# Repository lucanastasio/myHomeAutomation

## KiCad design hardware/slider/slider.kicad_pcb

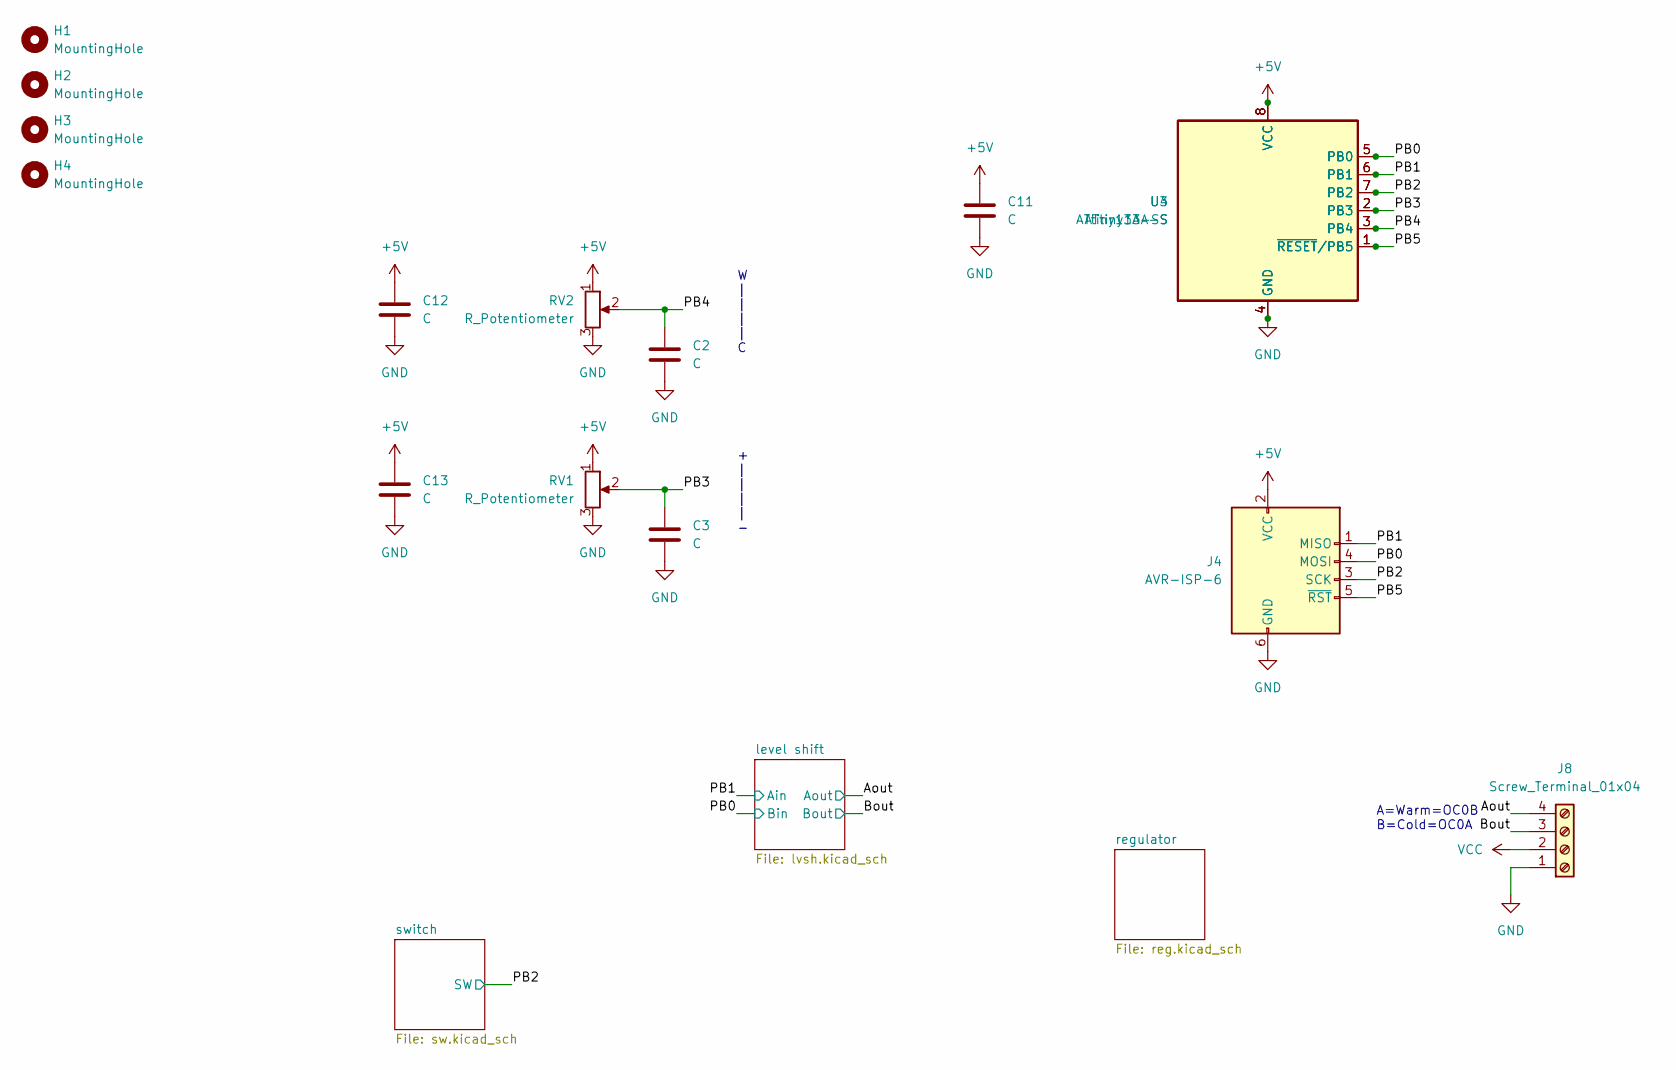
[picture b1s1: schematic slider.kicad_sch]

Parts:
C2, C3, C11, C12, C13: C; C_0603_1608Metric_Pad1.08x0.95mm_HandSolder
H1, H2, H3, H4: MountingHole; MountingHole_2.1mm
J4: AVR-ISP-6; PinHeader_2x03_P2.54mm_Vertical
J8: Screw_Terminal_01x04; PhoenixContact_MCV_1,5_4-G-3.81_1x04_P3.81mm_Vertical
RV1, RV2: R_Potentiometer; Alpha_RA2043F-20
U3: ATtiny13A-S; SOIC-8W_5.3x5.3mm_P1.27mm
U4: ATtiny13A-SS; SOIC-8_3.9x4.9mm_P1.27mm

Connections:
+5V: C11.1, C12.1, C13.1, J4.2 (VCC), RV1.1, RV2.1, U3.8 (VCC), U4.8 (VCC); also elsewhere on the board
/Aout: J8.4; also elsewhere on the board
/Bout: J8.3; also elsewhere on the board
/PB0: J4.4 (MOSI), U3.5 (PB0), U4.5 (PB0); also elsewhere on the board
/PB1: J4.1 (MISO), U3.6 (PB1), U4.6 (PB1); also elsewhere on the board
/PB2: J4.3 (SCK), U3.7 (PB2), U4.7 (PB2); also elsewhere on the board
/PB3: C3.1, RV1.2, U3.2 (PB3), U4.2 (PB3)
/PB4: C2.1, RV2.2, U3.3 (PB4), U4.3 (PB4)
/PB5: J4.5 (~RST), U3.1 (~RESET/PB5), U4.1 (~RESET/PB5)
GND: C2.2, C3.2, C11.2, C12.2, C13.2, J4.6 (GND), J8.1, RV1.3, RV2.3, U3.4 (GND), U4.4 (GND); also elsewhere on the board
VCC: J8.2; also elsewhere on the board

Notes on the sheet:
+ | | | | -
A=Warm=OC0B B=Cold=OC0A
W | | | | C

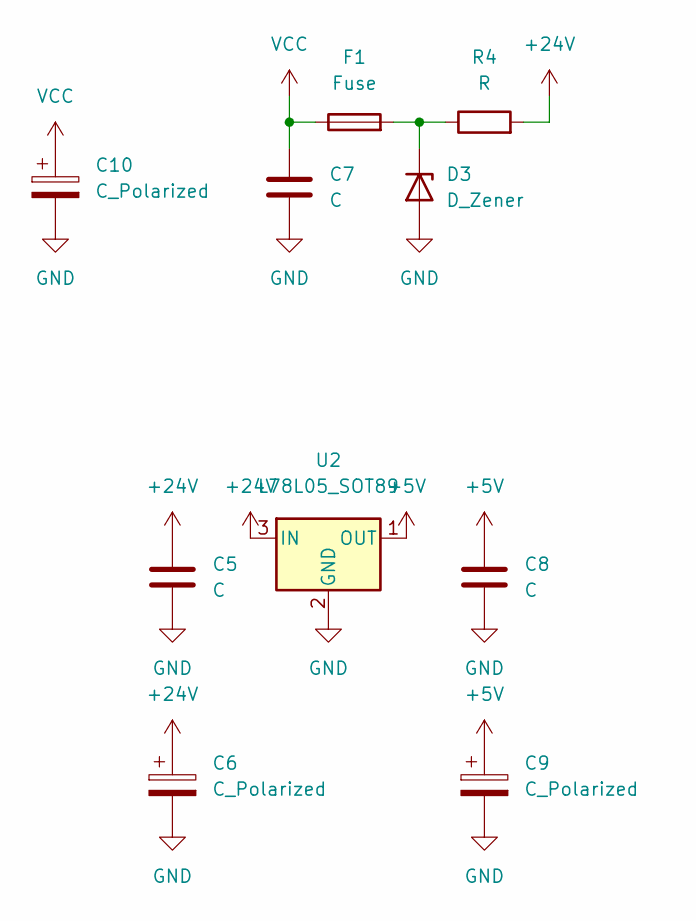
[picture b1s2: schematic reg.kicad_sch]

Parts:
C5, C7, C8: C; C_0603_1608Metric_Pad1.08x0.95mm_HandSolder
C6, C9: C_Polarized; CP_Elec_6.3x5.4
C10: C_Polarized; CP_Elec_8x6.7
D3: D_Zener; Nexperia_CFP3_SOD-123W
F1: Fuse; Fuse_1206_3216Metric_Pad1.42x1.75mm_HandSolder
R4: R; R_0805_2012Metric_Pad1.20x1.40mm_HandSolder
U2: L78L05_SOT89; SOT-89-3

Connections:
+5V: C8.1, C9.1, U2.1 (OUT); also elsewhere on the board
+24V: C5.1, C6.1, R4.2, U2.3 (IN); also elsewhere on the board
GND: C5.2, C6.2, C7.2, C8.2, C9.2, C10.2, D3.2 (A), U2.2 (GND); also elsewhere on the board
unnamed: D3.1 (K), F1.2, R4.1
VCC: C7.1, C10.1, F1.1; also elsewhere on the board

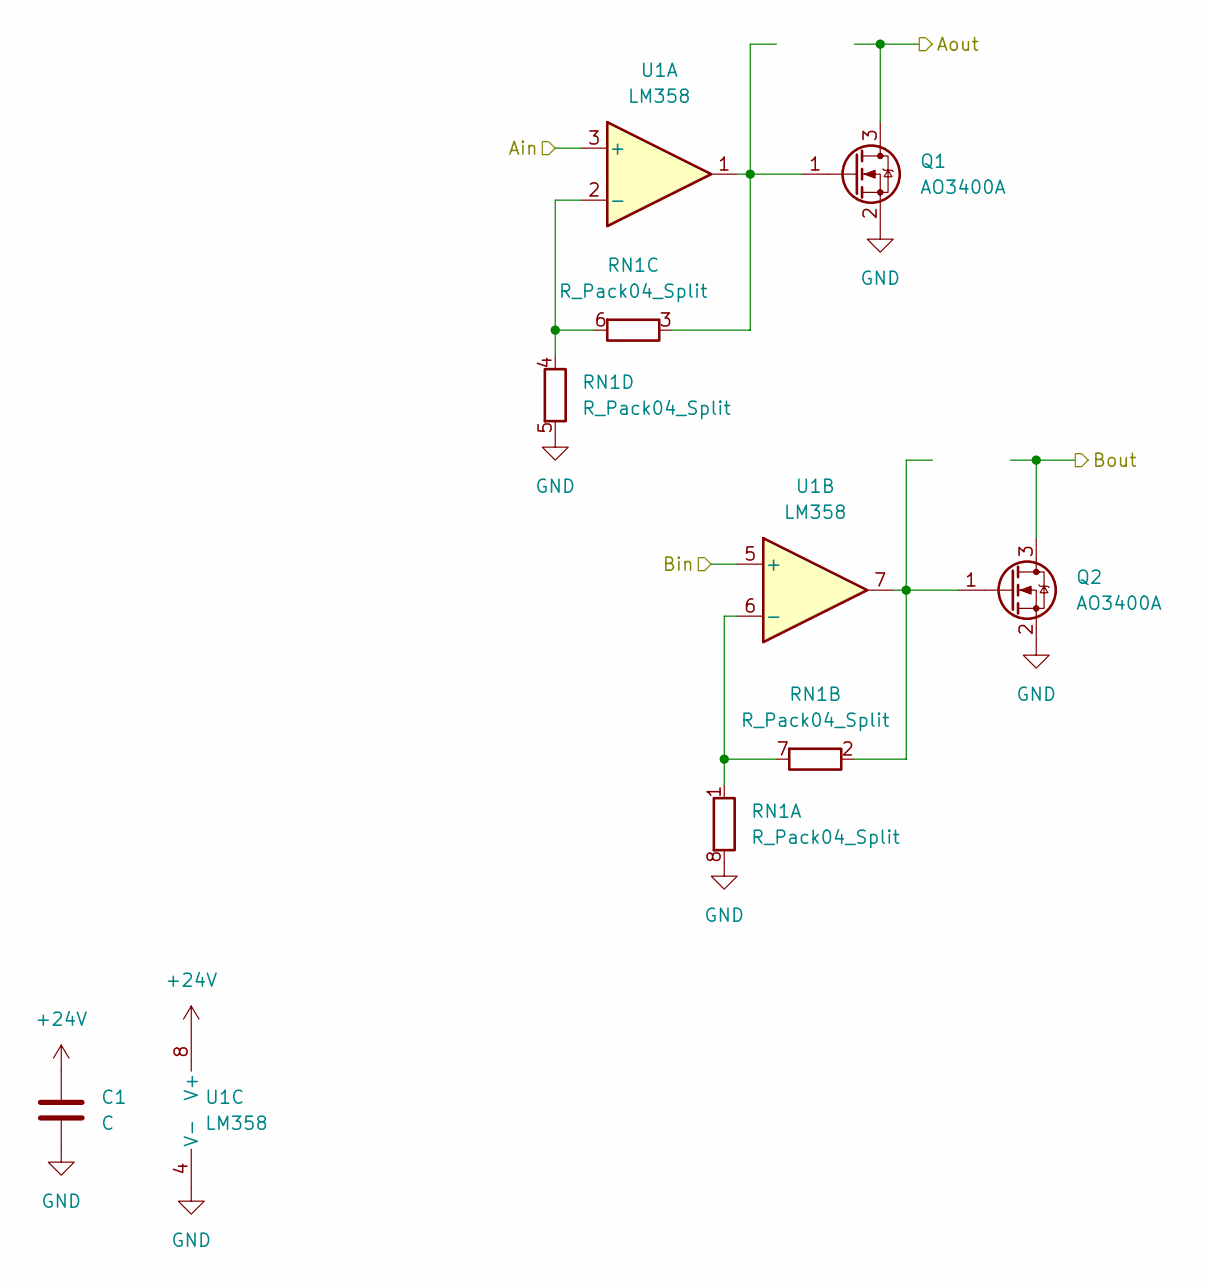
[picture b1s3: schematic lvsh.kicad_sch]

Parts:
C1: C; C_0603_1608Metric_Pad1.08x0.95mm_HandSolder
Q1, Q2: AO3400A; SOT-23W_Handsoldering
RN1: R_Pack04_Split; R_Array_Convex_4x0603
U1: LM358; SOIC-8_3.9x4.9mm_P1.27mm

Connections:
+24V: C1.1, U1.8 (V+); also elsewhere on the board
/Aout: Q1.3 (D); also elsewhere on the board
/Bout: Q2.3 (D); also elsewhere on the board
/PB0: U1.5 (+); also elsewhere on the board
/PB1: U1.3 (+); also elsewhere on the board
GND: C1.2, Q1.2 (S), Q2.2 (S), RN1.5 (R4.2), RN1.8 (R1.2), U1.4 (V-); also elsewhere on the board
unnamed: Q1.1 (G), RN1.3 (R3.1), U1.1
unnamed: Q2.1 (G), RN1.2 (R2.1), U1.7
unnamed: RN1.1 (R1.1), RN1.7 (R2.2), U1.6 (-)
unnamed: RN1.4 (R4.1), RN1.6 (R3.2), U1.2 (-)

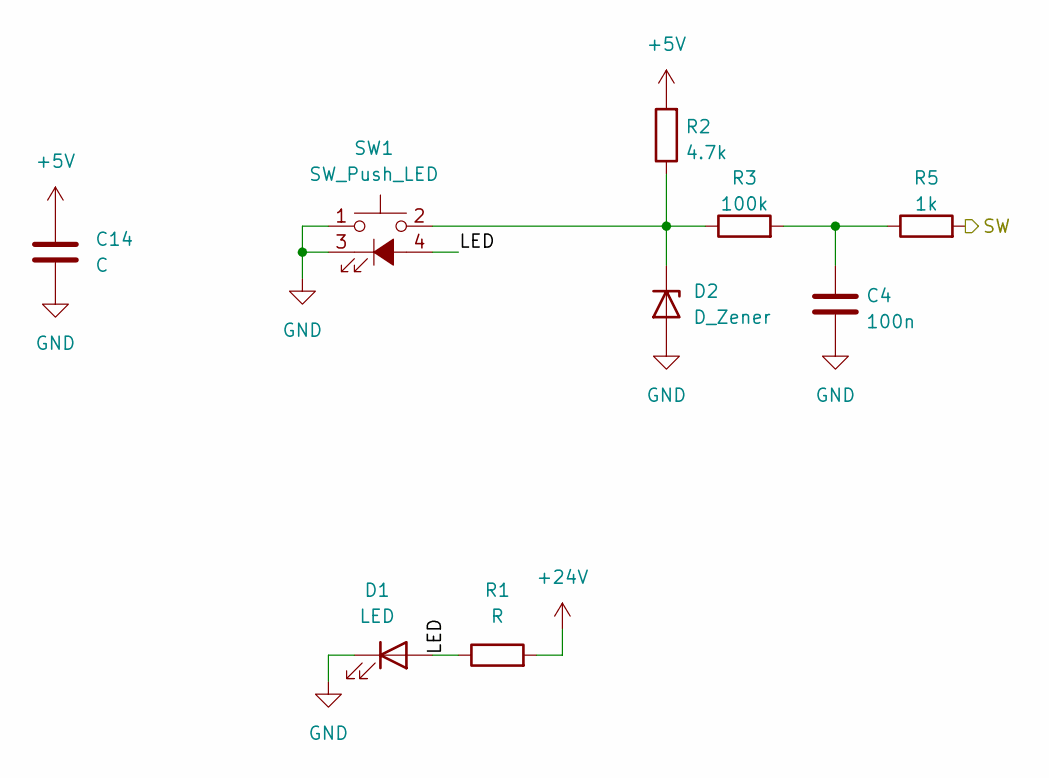
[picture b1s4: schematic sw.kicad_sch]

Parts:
C4: 100n; C_0603_1608Metric_Pad1.08x0.95mm_HandSolder
C14: C; C_0603_1608Metric_Pad1.08x0.95mm_HandSolder
D1: LED; LED_D5.0mm_Clear
D2: D_Zener; Nexperia_CFP3_SOD-123W
R1: R; R_0603_1608Metric_Pad0.98x0.95mm_HandSolder
R2: 4.7k; R_0603_1608Metric_Pad0.98x0.95mm_HandSolder
R3: 100k; R_0603_1608Metric_Pad0.98x0.95mm_HandSolder
R5: 1k; R_0603_1608Metric_Pad0.98x0.95mm_HandSolder
SW1: SW_Push_LED; SW_PUSH-12mm_LED

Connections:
+5V: C14.1, R2.2; also elsewhere on the board
+24V: R1.2; also elsewhere on the board
/PB2: R5.2; also elsewhere on the board
/switch/LED: D1.2 (A), R1.1, SW1.4 (A)
GND: C4.2, C14.2, D1.1 (K), D2.2 (A), SW1.1, SW1.3 (K); also elsewhere on the board
unnamed: C4.1, R3.2, R5.1
unnamed: D2.1 (K), R2.1, R3.1, SW1.2

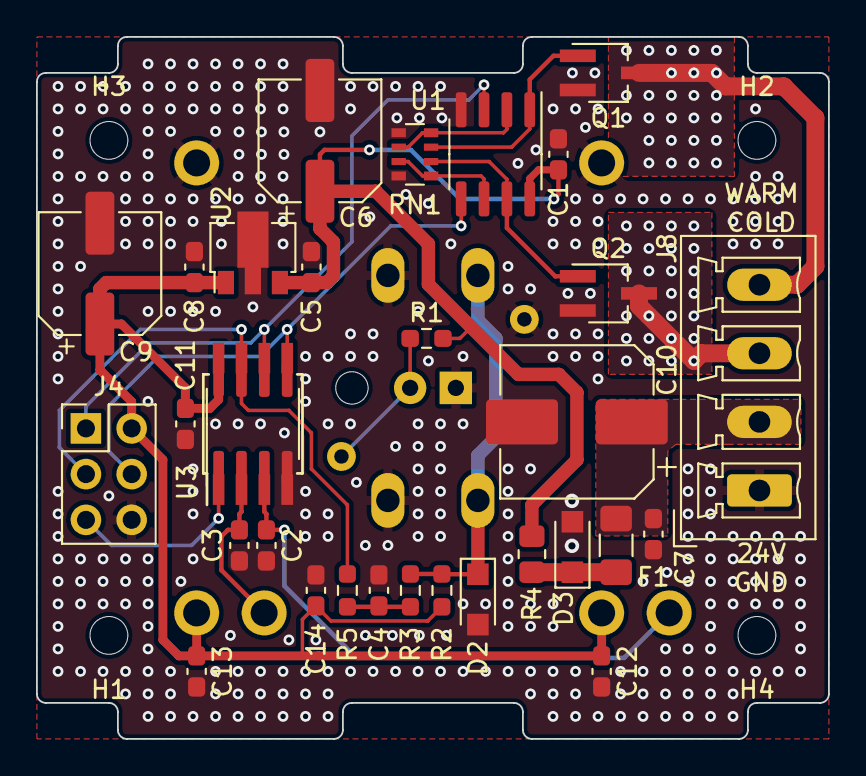
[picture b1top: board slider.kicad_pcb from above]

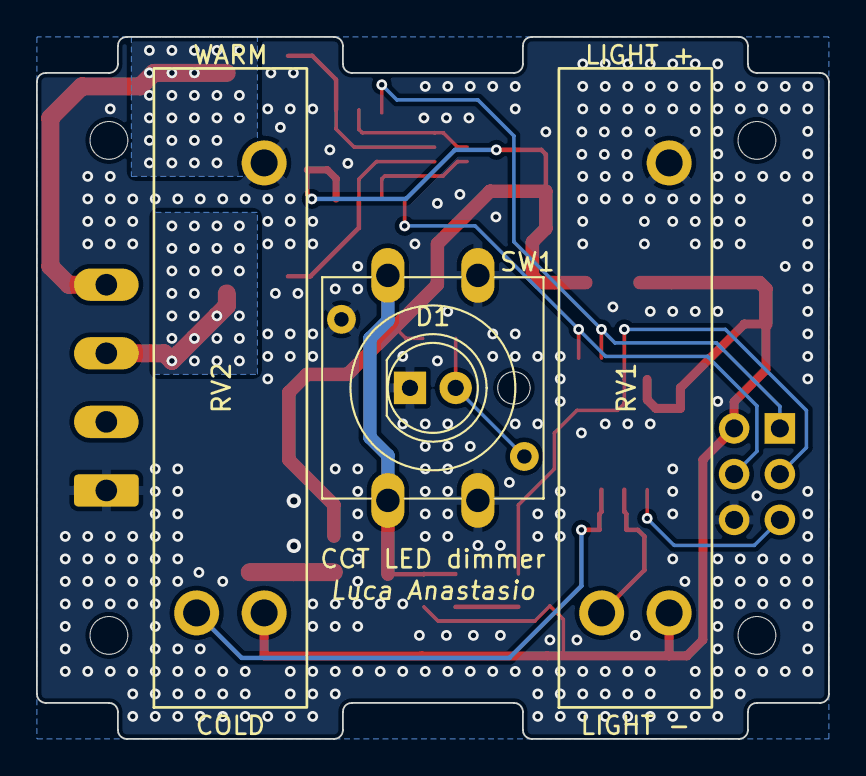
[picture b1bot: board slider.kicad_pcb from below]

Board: 2 copper layers, 44.0 x 39.0 mm, 39 parts (4 on the bottom side), 20 nets.

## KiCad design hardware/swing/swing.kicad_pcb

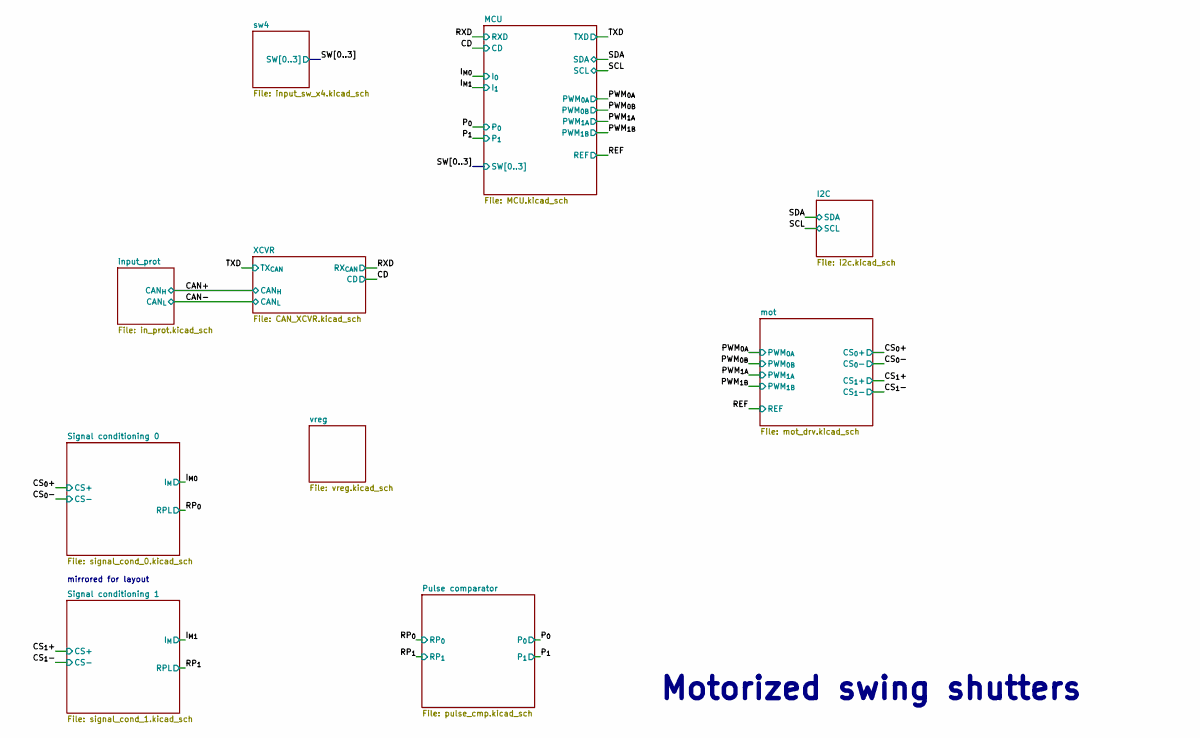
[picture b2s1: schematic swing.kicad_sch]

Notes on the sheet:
Motorized swing shutters
mirrored for layout

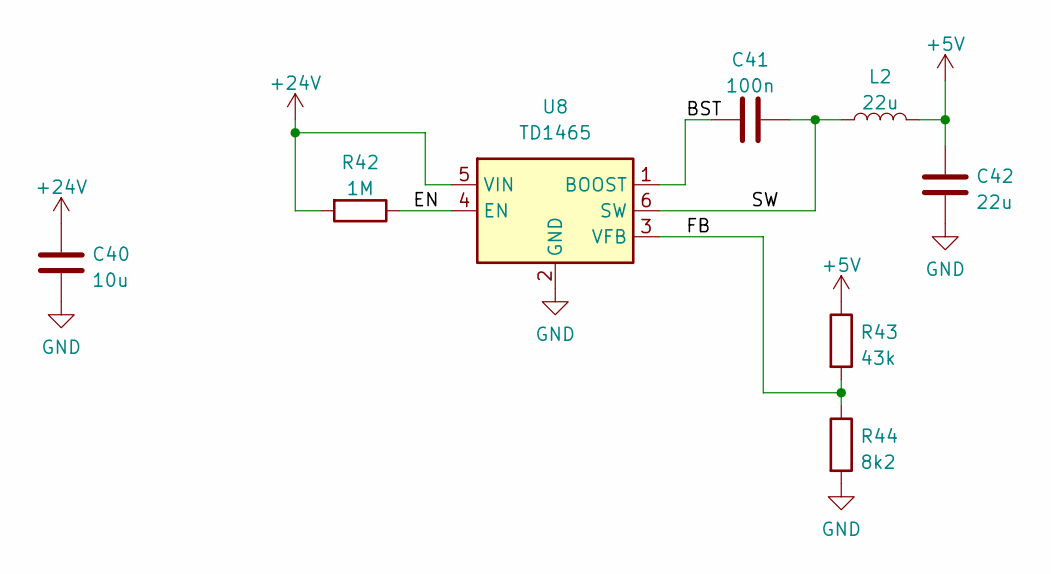
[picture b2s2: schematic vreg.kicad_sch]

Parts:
C40: 10u; C_1206_3216Metric
C41: 100n; C_0603_1608Metric
C42: 22u; C_0805_2012Metric
L2: 22u; L_1210_3225Metric
R42: 1M; R_0603_1608Metric
R43: 43k; R_0603_1608Metric
R44: 8k2; R_0603_1608Metric
U8: TD1465; SOT-23-6

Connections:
+5V: C42.2, L2.2, R43.1; also elsewhere on the board
+24V: C40.2, R42.2, U8.5 (VIN); also elsewhere on the board
/vreg/BST: C41.1, U8.1 (BOOST)
/vreg/EN: R42.1, U8.4 (EN)
/vreg/FB: R43.2, R44.1, U8.3 (VFB)
/vreg/SW: C41.2, L2.1, U8.6 (SW)

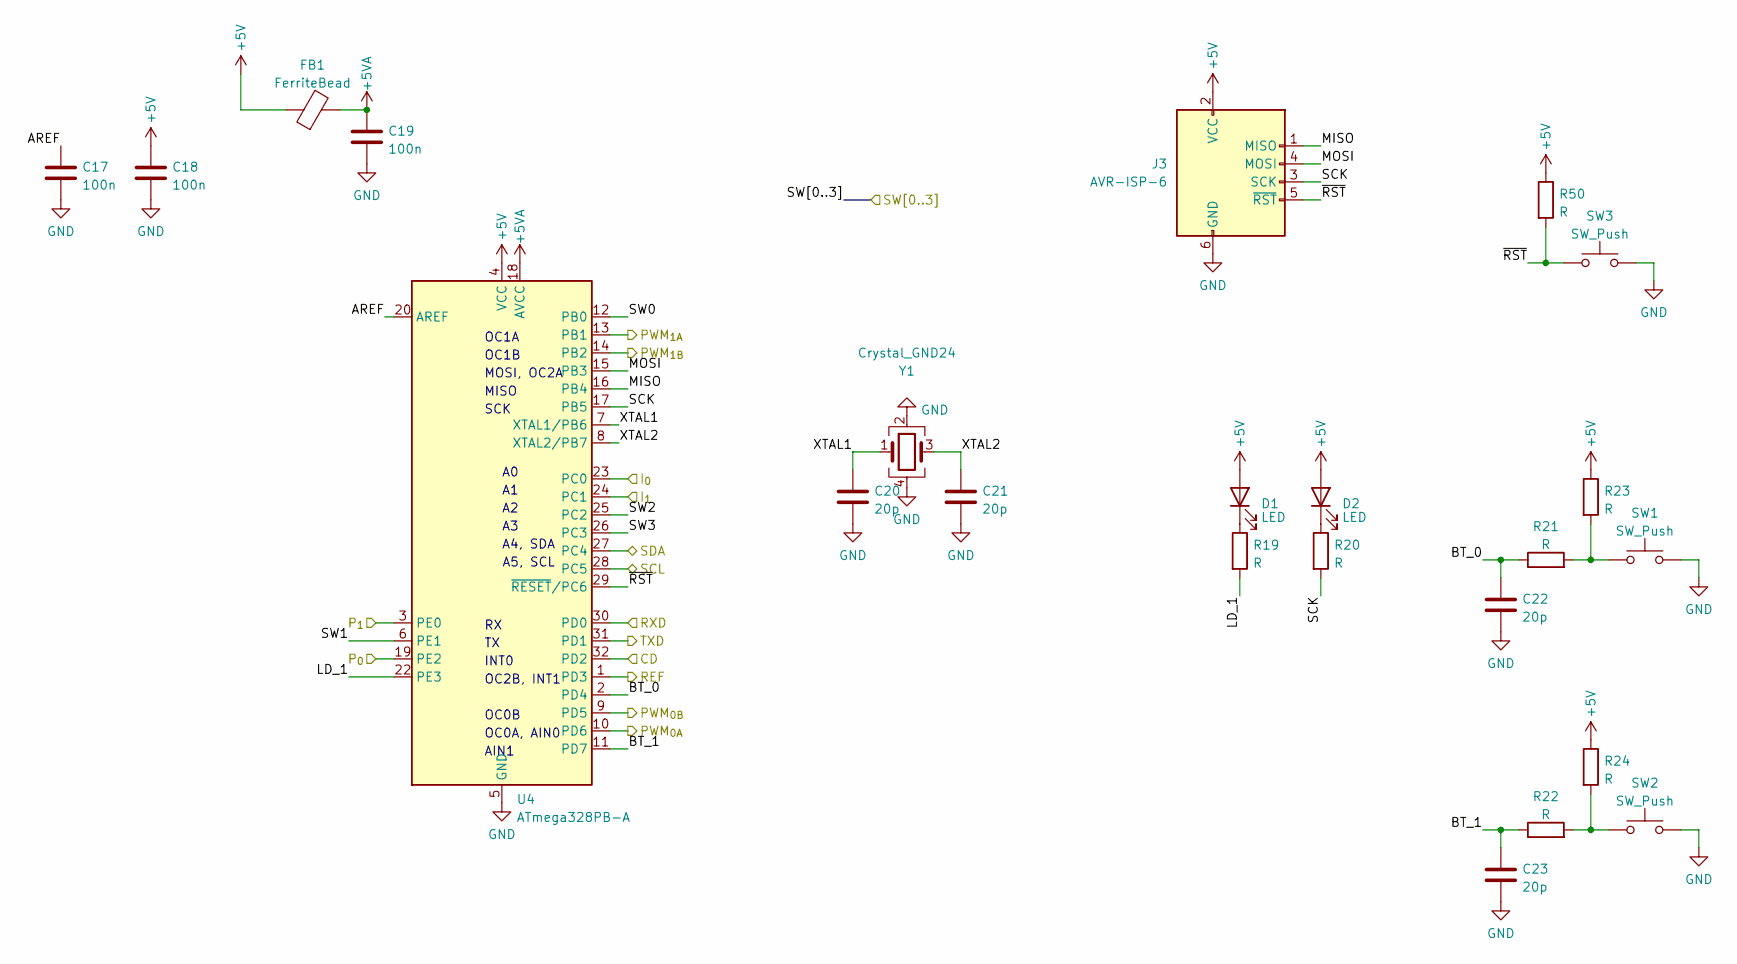
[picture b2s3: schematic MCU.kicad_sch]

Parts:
C17, C18, C19: 100n; C_0603_1608Metric
C20, C21, C22, C23: 20p; C_0402_1005Metric
D1, D2: LED; LED_0603_1608Metric
FB1: FerriteBead; L_0603_1608Metric
J3: AVR-ISP-6; Tag-Connect_TC2030-IDC-NL_2x03_P1.27mm_Vertical
R19, R20, R21, R22, R23, R24, R50: R; R_0402_1005Metric
SW1, SW2, SW3: SW_Push; SW_SPST_B3U-1000P
U4: ATmega328PB-A; TQFP-32_7x7mm_P0.8mm
Y1: Crystal_GND24; Crystal_SMD_3225-4Pin_3.2x2.5mm

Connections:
+5V: C18.2, D1.2 (A), D2.2 (A), FB1.1, J3.2 (VCC), R23.1, R24.1, R50.1, U4.4 (VCC); also elsewhere on the board
+5VA: C19.1, FB1.2, U4.18 (AVCC); also elsewhere on the board
/CD: U4.32 (PD2); also elsewhere on the board
/I_{M0}: U4.23 (PC0); also elsewhere on the board
/I_{M1}: U4.24 (PC1); also elsewhere on the board
/MCU/AREF: C17.1, U4.20 (AREF)
/MCU/BT_0: C22.1, R21.1, U4.2 (PD4)
/MCU/BT_1: C23.1, R22.1, U4.11 (PD7)
/MCU/LD_1: R19.2, U4.22 (PE3)
/MCU/MISO: J3.1 (MISO), U4.16 (PB4)
/MCU/MOSI: J3.4 (MOSI), U4.15 (PB3)
/MCU/SCK: J3.3 (SCK), R20.2, U4.17 (PB5)
/MCU/XTAL1: C20.1, U4.7 (XTAL1/PB6), Y1.1
/MCU/XTAL2: C21.1, U4.8 (XTAL2/PB7), Y1.3
/MCU/~RST: J3.5 (~RST), R50.2, SW3.1, U4.29 (~RESET/PC6)
/PWM_{0A}: U4.10 (PD6); also elsewhere on the board
/PWM_{0B}: U4.9 (PD5); also elsewhere on the board
/PWM_{1A}: U4.13 (PB1); also elsewhere on the board
/PWM_{1B}: U4.14 (PB2); also elsewhere on the board
/P_{0}: U4.19 (PE2); also elsewhere on the board
/P_{1}: U4.3 (PE0); also elsewhere on the board
/REF: U4.1 (PD3); also elsewhere on the board
/RXD: U4.30 (PD0); also elsewhere on the board
/SCL: U4.28 (PC5); also elsewhere on the board
/SDA: U4.27 (PC4); also elsewhere on the board
/SW0: U4.12 (PB0); also elsewhere on the board
/SW1: U4.6 (PE1); also elsewhere on the board
/SW2: U4.25 (PC2); also elsewhere on the board
/SW3: U4.26 (PC3); also elsewhere on the board
/TXD: U4.31 (PD1); also elsewhere on the board
unnamed: D1.1 (K), R19.1
unnamed: D2.1 (K), R20.1
unnamed: R21.2, R23.2, SW1.1
unnamed: R22.2, R24.2, SW2.1

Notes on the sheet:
A4, SDA
AIN1
OC2B, INT1
SCK
MOSI, OC2A
OC0A, AIN0
A5, SCL
OC1B
INT0
MISO
OC0B
OC1A

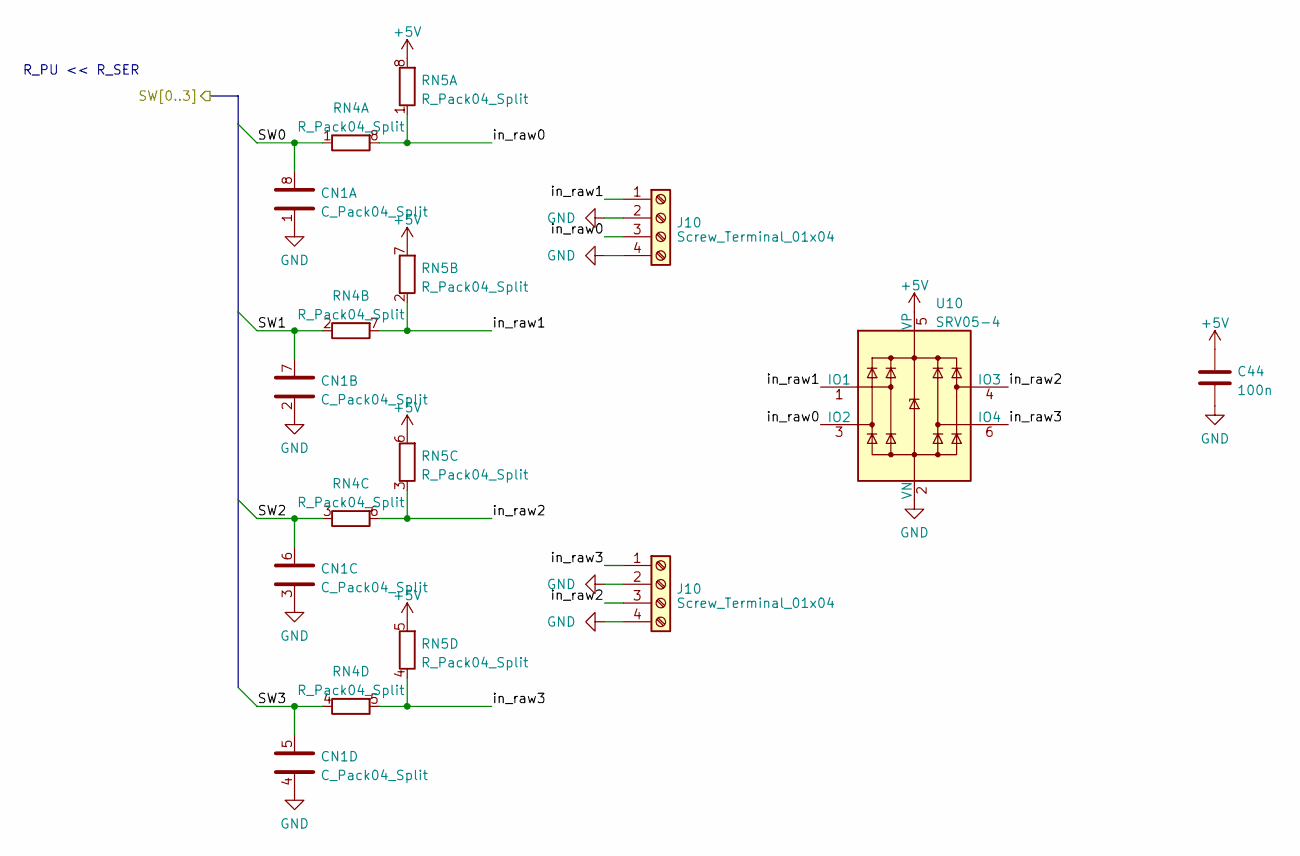
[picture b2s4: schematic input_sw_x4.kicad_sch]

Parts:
C44: 100n; C_0603_1608Metric
CN1: C_Pack04_Split; R_Array_Convex_4x0603
J10: Screw_Terminal_01x04; TerminalBlock_TE_282834-4_1x04_P2.54mm_Horizontal
RN4, RN5: R_Pack04_Split; R_Array_Convex_4x0603
U10: SRV05-4; SOT-23-6

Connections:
+5V: C44.1, RN5.5 (R4.2), RN5.6 (R3.2), RN5.7 (R2.2), RN5.8 (R1.2), U10.5 (VP); also elsewhere on the board
/SW0: CN1.8 (R1.2), RN4.1 (R1.1); also elsewhere on the board
/SW1: CN1.7 (R2.2), RN4.2 (R2.1); also elsewhere on the board
/SW2: CN1.6 (R3.2), RN4.3 (R3.1); also elsewhere on the board
/SW3: CN1.5 (R4.2), RN4.4 (R4.1); also elsewhere on the board

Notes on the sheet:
R_PU << R_SER

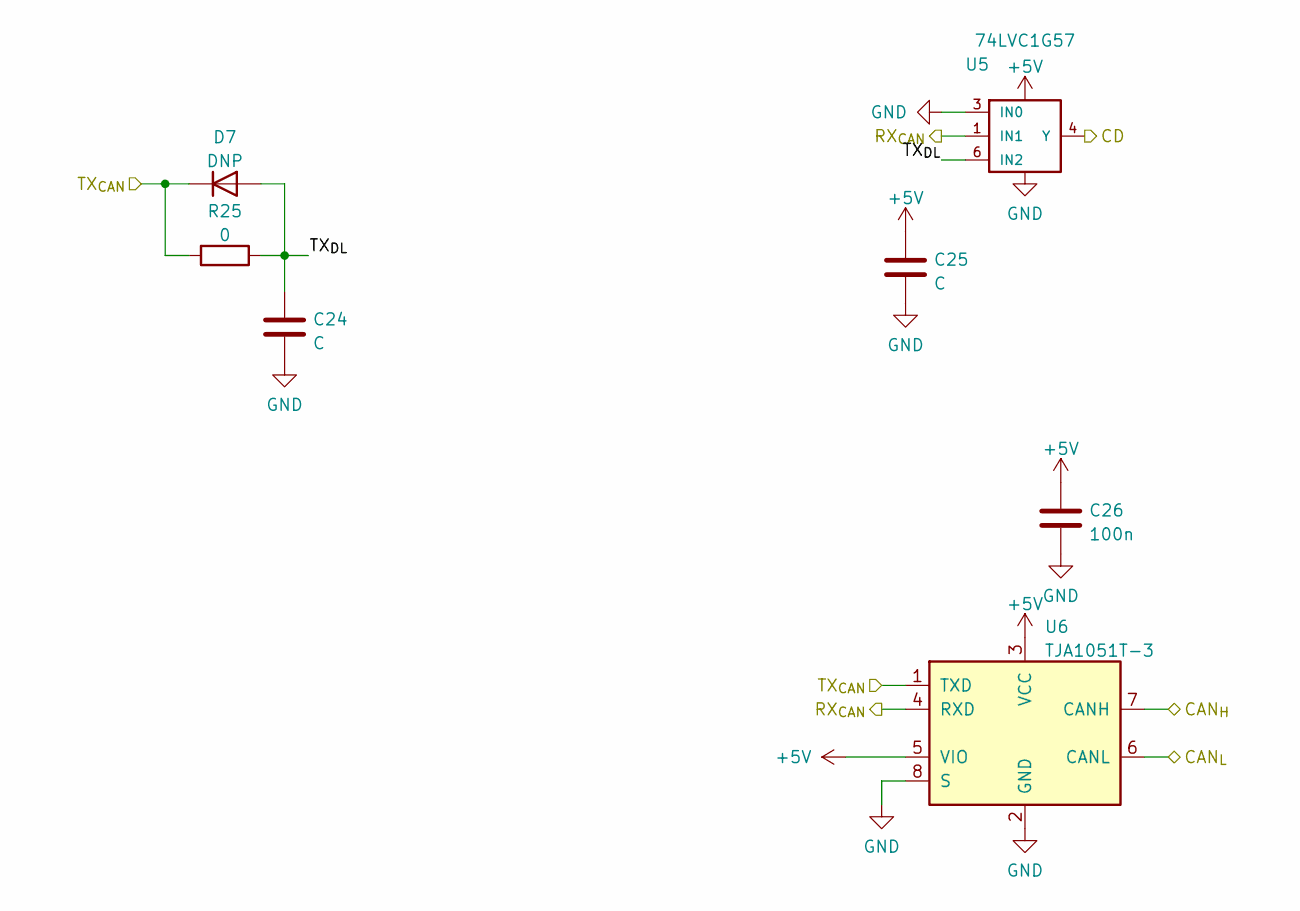
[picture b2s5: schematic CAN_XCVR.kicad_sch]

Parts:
C24, C25: C; C_0402_1005Metric
C26: 100n; C_0603_1608Metric
D7: DNP; D_SOD-523
R25: 0; R_0402_1005Metric
U5: 74LVC1G57; SOT-563
U6: TJA1051T-3; SOIC-8_3.9x4.9mm_P1.27mm

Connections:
+5V: C25.1, C26.2, U5.5 (VCC), U6.3 (VCC), U6.5 (VIO); also elsewhere on the board
/CAN+: U6.7 (CANH); also elsewhere on the board
/CAN-: U6.6 (CANL); also elsewhere on the board
/CD: U5.4 (Y); also elsewhere on the board
/RXD: U5.1 (IN1), U6.4 (RXD); also elsewhere on the board
/TXD: D7.1 (K), R25.2, U6.1 (TXD); also elsewhere on the board
/XCVR/TX_{DL}: C24.1, D7.2 (A), R25.1, U5.6 (IN2)

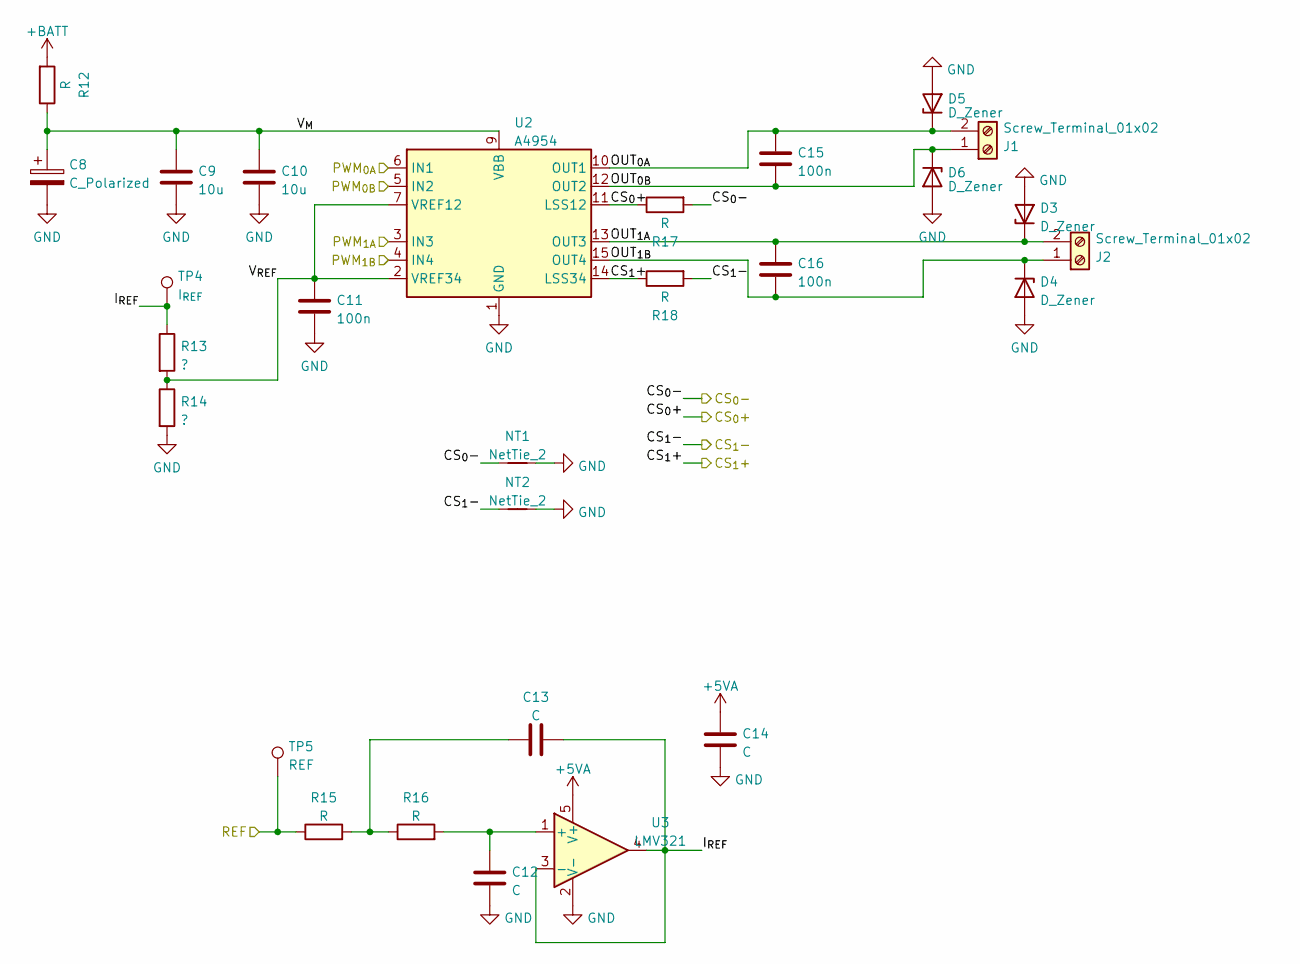
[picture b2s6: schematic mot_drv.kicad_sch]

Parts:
C8: C_Polarized; CP_Radial_D10.0mm_P5.00mm
C9, C10: 10u; C_1206_3216Metric
C11: 100n; C_0402_1005Metric
C12, C13, C14: C; C_0402_1005Metric
C15, C16: 100n; C_0805_2012Metric_Pad1.18x1.45mm_HandSolder
D3, D4, D5, D6: D_Zener; D_SOD-123F
J1, J2: Screw_Terminal_01x02; PhoenixContact_MCV_1,5_2-G-3.81_1x02_P3.81mm_Vertical
NT1, NT2: NetTie_2; NetTie-2_SMD_Pad0.5mm
R12: R; R_2512_6332Metric
R13, R14: ?; R_0402_1005Metric
R15, R16: R; R_0402_1005Metric
R17, R18: R; R_0805_2012Metric
TP4: I_{REF}; TestPoint_THTPad_D1.0mm_Drill0.5mm
TP5: REF; TestPoint_THTPad_D1.0mm_Drill0.5mm
U2: A4954; TSSOP-16-1EP_4.4x5mm_P0.65mm_EP3x3mm_ThermalVias
U3: LMV321; SOT-353_SC-70-5

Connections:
+5VA: C14.2, U3.5 (V+); also elsewhere on the board
+BATT: R12.2; also elsewhere on the board
/CS_{0}+: R17.1, U2.11 (LSS12); also elsewhere on the board
/CS_{0}-: NT1.1, R17.2; also elsewhere on the board
/CS_{1}+: R18.1, U2.14 (LSS34); also elsewhere on the board
/CS_{1}-: NT2.1, R18.2; also elsewhere on the board
/PWM_{0A}: U2.6 (IN1); also elsewhere on the board
/PWM_{0B}: U2.5 (IN2); also elsewhere on the board
/PWM_{1A}: U2.3 (IN3); also elsewhere on the board
/PWM_{1B}: U2.4 (IN4); also elsewhere on the board
/REF: R15.1, TP5.1; also elsewhere on the board
/mot/I_{REF}: C13.2, R13.1, TP4.1, U3.3 (-), U3.4
/mot/OUT_{0A}: C15.2, D5.1 (K), J1.2, U2.10 (OUT1)
/mot/OUT_{0B}: C15.1, D6.1 (K), J1.1, U2.12 (OUT2)
/mot/OUT_{1A}: C16.2, D3.1 (K), J2.2, U2.13 (OUT3)
/mot/OUT_{1B}: C16.1, D4.1 (K), J2.1, U2.15 (OUT4)
/mot/V_{M}: C8.1, C9.2, C10.2, R12.1, U2.9 (VBB), U2.16 (VBB)
/mot/V_{REF}: C11.2, R13.2, R14.1, U2.2 (VREF34), U2.7 (VREF12)
unnamed: C13.1, R15.2, R16.1
unnamed: C12.1, R16.2, U3.1 (+)

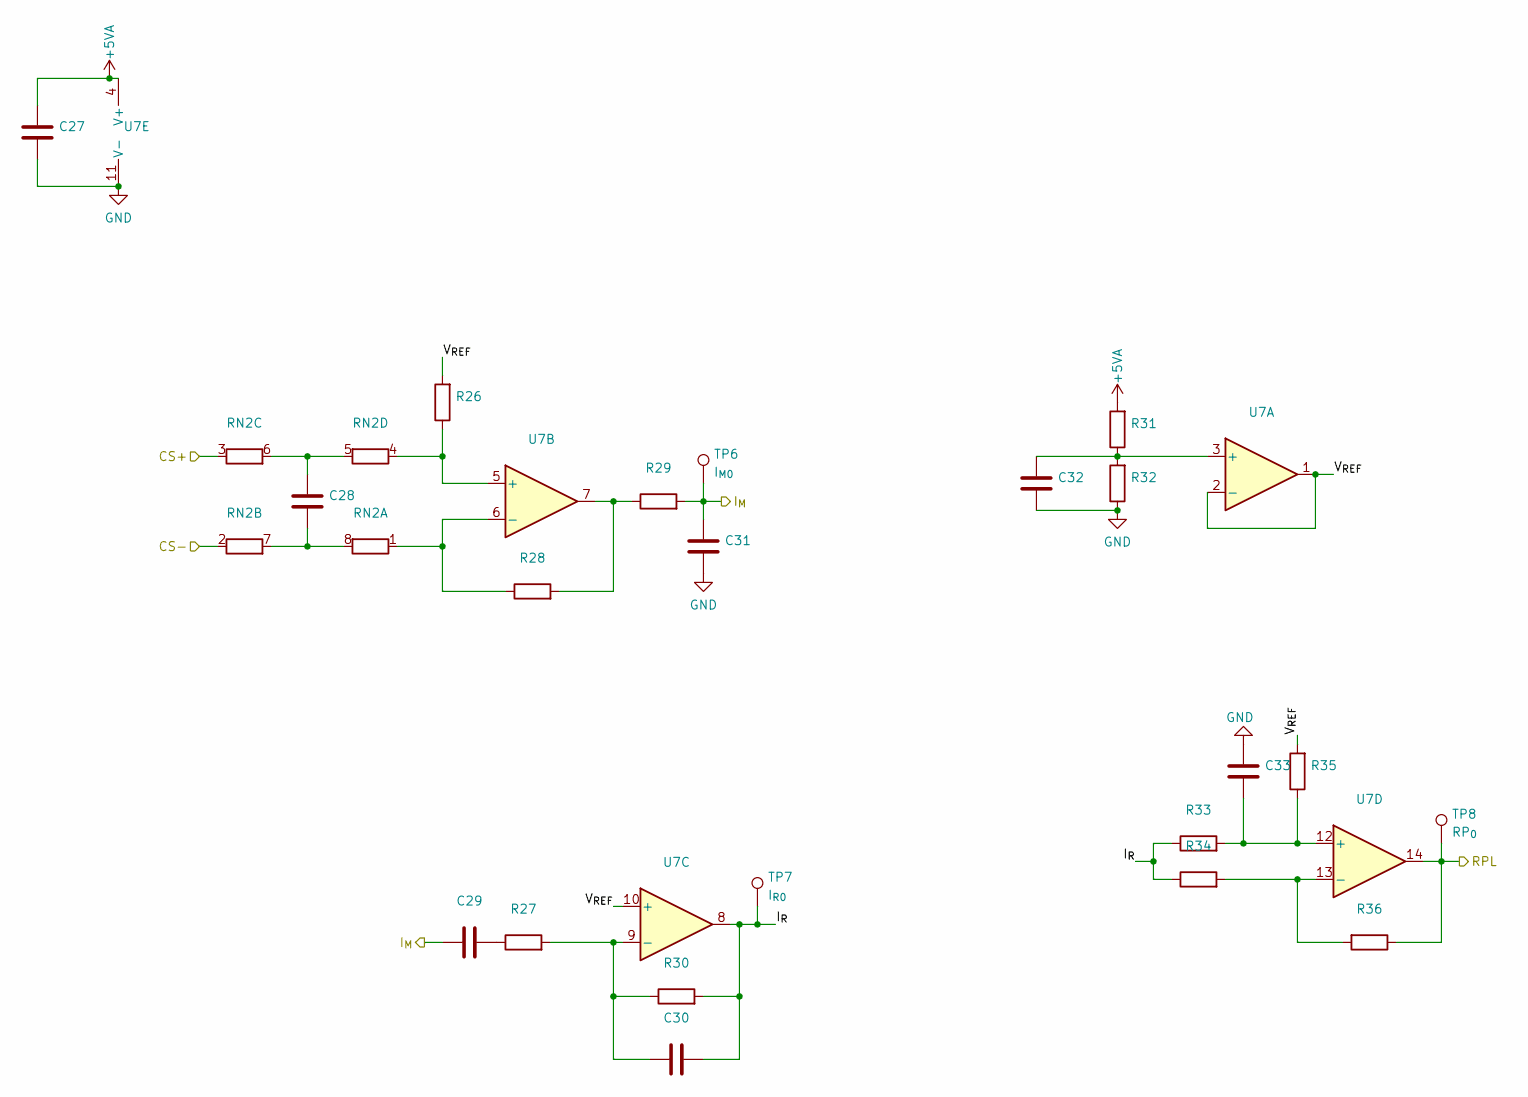
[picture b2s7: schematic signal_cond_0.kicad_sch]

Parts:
C27, C28, C29, C30, C31, C32, C33: C_0402_1005Metric
R26, R27, R28, R29, R30, R31, R32, R33, R34, R35, R36: R_0402_1005Metric
RN2: R_Array_Convex_4x0402
TP6: I_{M0}; TestPoint_THTPad_D1.0mm_Drill0.5mm
TP7: I_{R0}; TestPoint_THTPad_D1.0mm_Drill0.5mm
TP8: RP_{0}; TestPoint_THTPad_D1.0mm_Drill0.5mm
U7: TSSOP-14_4.4x5mm_P0.65mm

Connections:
+5VA: C27.1, R31.2, U7.4 (V+); also elsewhere on the board
/CS_{0}+: RN2.3 (R3.1); also elsewhere on the board
/CS_{0}-: RN2.2 (R2.1); also elsewhere on the board
/I_{M0}: C29.1, C31.1, R29.2, TP6.1; also elsewhere on the board
/RP_{0}: R36.1, TP8.1, U7.14; also elsewhere on the board
/Signal conditioning 0/I_{R}: C30.2, R30.2, R33.1, R34.1, TP7.1, U7.8
/Signal conditioning 0/V_{REF}: R26.2, R35.2, U7.1, U7.2 (-), U7.10 (+)
unnamed: C29.2, R27.1
unnamed: R28.2, R29.1, U7.7
unnamed: R28.1, RN2.1 (R1.1), U7.6 (-)
unnamed: C28.2, RN2.7 (R2.2), RN2.8 (R1.2)
unnamed: C28.1, RN2.5 (R4.2), RN2.6 (R3.2)
unnamed: R26.1, RN2.4 (R4.1), U7.5 (+)
unnamed: C32.1, R31.1, R32.2, U7.3 (+)
unnamed: C30.1, R27.2, R30.1, U7.9 (-)
unnamed: C33.2, R33.2, R35.1, U7.12 (+)
unnamed: R34.2, R36.2, U7.13 (-)

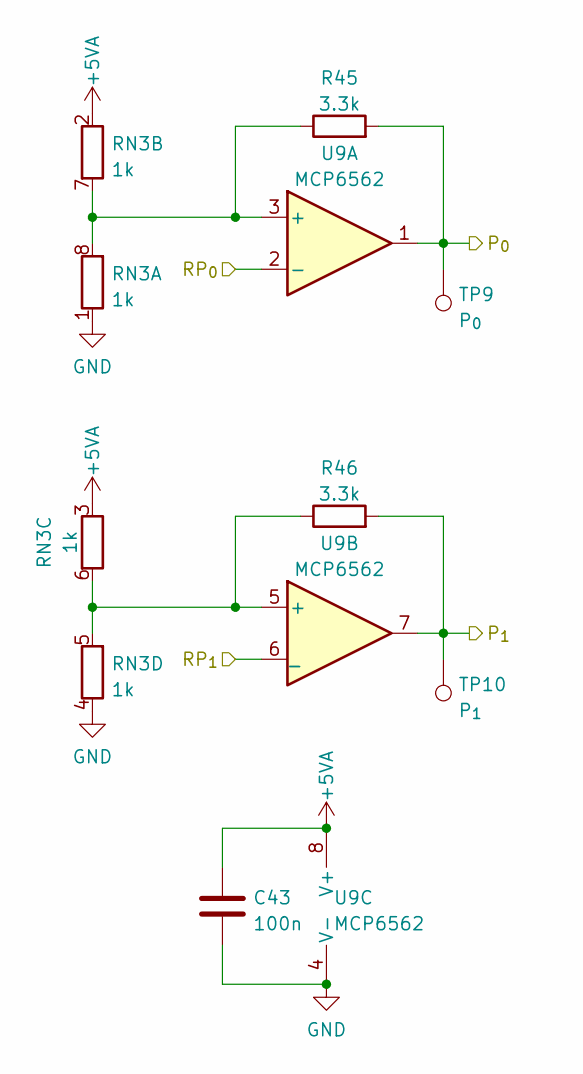
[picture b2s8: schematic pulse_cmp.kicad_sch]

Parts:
C43: 100n; C_0402_1005Metric
R45, R46: 3.3k; R_0402_1005Metric
RN3: 1k; R_Array_Convex_4x0402
TP9: P_{0}; TestPoint_THTPad_D1.0mm_Drill0.5mm
TP10: P_{1}; TestPoint_THTPad_D1.0mm_Drill0.5mm
U9: MCP6562; TSSOP-8_3x3mm_P0.65mm

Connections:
+5VA: C43.1, RN3.2 (R2.1), RN3.3 (R3.1), U9.8 (V+); also elsewhere on the board
/P_{0}: R45.2, TP9.1, U9.1; also elsewhere on the board
/P_{1}: R46.2, TP10.1, U9.7; also elsewhere on the board
/RP_{0}: U9.2 (-); also elsewhere on the board
/RP_{1}: U9.6 (_); also elsewhere on the board
unnamed: R45.1, RN3.7 (R2.2), RN3.8 (R1.2), U9.3 (+)
unnamed: R46.1, RN3.5 (R4.2), RN3.6 (R3.2), U9.5 (+)

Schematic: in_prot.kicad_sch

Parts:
C34, C35, C37, C39: C; C_0603_1608Metric
C36: C_Polarized; CP_Radial_D6.3mm_P2.50mm
C38: C; C_0805_2012Metric_Pad1.18x1.45mm_HandSolder
D8: D_Zener; D_SMA
D9: SM712_SOT23; SOT-23
F1: Fuse; Fuse_1206_3216Metric_Pad1.42x1.75mm_HandSolder
J4: Screw_Terminal_01x04; PhoenixContact_MCV_1,5_4-G-3.81_1x04_P3.81mm_Vertical
L1: L_Ferrite_Coupled; L_CommonModeChoke_Coilcraft_0805USB
R37: R; R_0805_2012Metric
R38, R41: R; R_0603_1608Metric
R39, R40: R; R_0805_2012Metric_Pad1.20x1.40mm_HandSolder

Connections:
+24V: C36.1, R37.2; also elsewhere on the board
+BATT: C34.1, C35.1, D8.1 (K), F1.2, R37.1; also elsewhere on the board
/CAN+: L1.2; also elsewhere on the board
/CAN-: L1.3; also elsewhere on the board
/input_prot/CAN_{Hin}: C39.1, D9.2 (A2), J4.2, R40.2, R41.1
/input_prot/CAN_{Lin}: C37.1, D9.1 (A1), J4.3, R38.1, R39.1
/input_prot/CAN_{SPLIT}: C38.1, R39.2, R40.1
/input_prot/Vin: F1.1, J4.1
unnamed: L1.1, R41.2
unnamed: L1.4, R38.2

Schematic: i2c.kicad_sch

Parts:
C45: 100n; C_0603_1608Metric
J10: Screw_Terminal_01x04; TerminalBlock_TE_282834-4_1x04_P2.54mm_Horizontal
R47: 1; R_0603_1608Metric
R48, R49: ?; R_0603_1608Metric
U11: USBLC6-2SC6; SOT-23-6

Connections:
+5V: R47.1, R48.1, R49.1; also elsewhere on the board
/SCL: R48.2, U11.6 (I/O1); also elsewhere on the board
/SDA: R49.2, U11.4 (I/O2); also elsewhere on the board
